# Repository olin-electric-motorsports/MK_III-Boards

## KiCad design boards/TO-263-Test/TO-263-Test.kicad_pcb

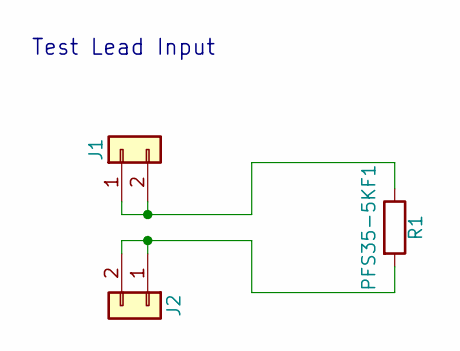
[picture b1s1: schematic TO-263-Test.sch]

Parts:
J1, J2: Conn_01x02; Pin_Header_Straight_1x02_Pitch2.54mm
R1: PFS35-5KF1; TO-263-2-Heatsink

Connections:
unnamed: J1.1, J1.2, R1.1
unnamed: J2.1, J2.2, R1.2

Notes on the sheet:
Test Lead Input

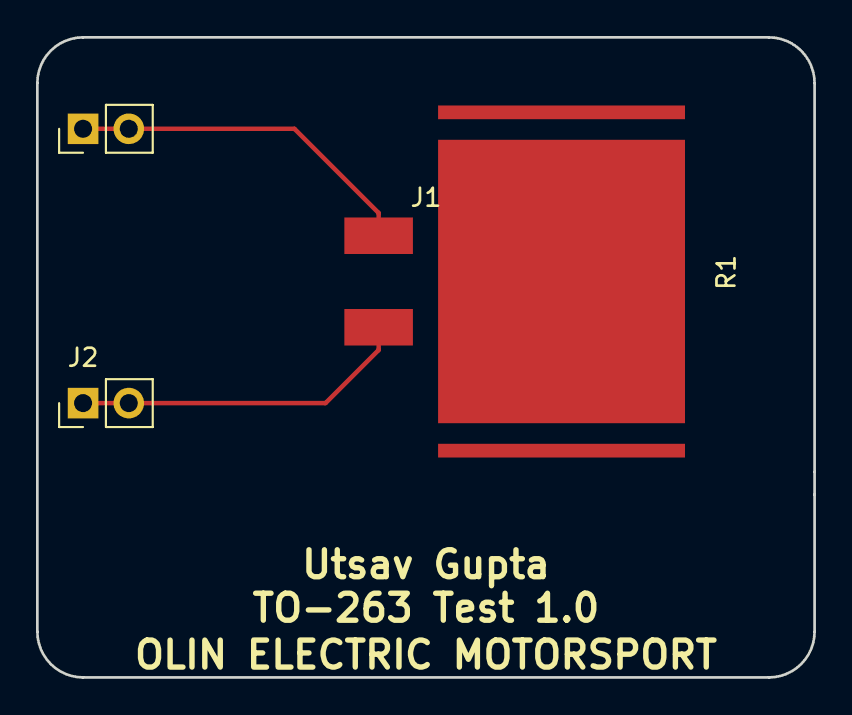
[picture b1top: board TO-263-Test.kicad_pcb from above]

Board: 2 copper layers, 43.2 x 35.6 mm, 3 parts (0 on the bottom side), 2 nets.

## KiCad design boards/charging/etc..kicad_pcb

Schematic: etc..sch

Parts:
C1, C2, C8, C9, C10: C_0.1uF; C_0805_OEM; MPN 478-3352-1-ND
C3: C_100pF; C_0805_OEM; MPN 399-1122-1-ND
C4, C5, C6, C7: C_30pF; C_0805_OEM; MPN 1276-1130-1-ND
C11: C_1uF; C_0805_OEM; MPN 478-10487-1-ND
C12: C_47uF; C_0805_OEM; MPN 587-4280-1-ND
C13: C_22uF; C_0805_OEM; MPN 1276-2725-1-ND
D1, D2, D3, D4, D8, D9: LED_0805; LED_0805_OEM; MPN 475-1410-1-ND
D7: D_Zener_18V; DO-214AA; MPN SMBJ5355B-TPMSCT-ND
F1: F_500mA_16V; Fuse_1210; MPN 507-1786-1-ND
IC1: ATMEGA16M1; TQFP-32_7x7mm_Pitch0.8mm; MPN ATMEGA16M1-AU-ND
J1: LCD screen; micromatch_female_vert_16; MPN A116164CT-ND
J2: Ampseal_8
J3, J4: Ultrafit_4; MPN WM11574-ND
L1: L_4.7uH; 4.7uH_Inductor_OEM; MPN 445-6583-1-ND
P1, P2: CONN_02X03; Pin_Header_Straight_2x03; MPN 609-3234-ND
R1: R_100; R_0805_OEM; MPN RNCP0805FTD100RCT-ND
R2, R3, R6, R16, R17: R_10k; R_0805_OEM; MPN CRS0805-FX-1002ELFCT-ND
R4, R5, R7, R8, R9, R10, R14: R_200; R_0805_OEM; MPN RMCF0805JT200RCT-ND
R13: R_0_Jumper; R_2512_OEM; MPN A121322CT-ND
R15: R_55.1k; R_0805_OEM; MPN 311-51.1KCRCT-ND
R18: R_1k; R_0805_OEM; MPN RNCP0805FTD1K00CT-ND
RV1: POT_TRIM-device; Potentiometer_Trimmer_Bourns_TCC3
U1: ATMEGA328P-AU; TQFP-32_7x7mm_Pitch0.8mm
U2: CAN_Transceiver; SOIC-8_3.9x4.9mm_Pitch1.27mm_OEM; MPN MCP2561-E/SN-ND
U3: RJ45_VT; RJ45-Vertical; MPN MRJ-5481-01-ND
U4: TPS561201; SOT-23-6_OEM; MPN TPS561201
Y1, Y2: Crystal_SMD; Crystal_SMD_FA238; MPN SER3686CT-ND

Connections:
+12V: D7.1, F1.1, J2.3, J2.5
AMS: IC1.15, J3.3
CANH: J2.4, J2.6, U2.7, U3.2
CANL: J2.7, J2.8, U2.6, U3.1
DATA: IC1.16, R3.1, U1.14
DB0: IC1.28, J1.7
DB1: IC1.27, J1.8
DB2: IC1.26, J1.9
DB3: IC1.25, J1.10
DB4: IC1.24, J1.11
DB5: IC1.23, J1.12
DB6: IC1.22, J1.13
DB7: IC1.18, J1.14
E: IC1.29, J1.6
GND: C1.2, C2.2, C3.2, C4.2, C5.2, C6.2, C7.2, C8.2, C9.1, C11.1, C12.2, C13.2, D1.1, D2.1, D3.1, D4.1, D7.2, D8.1, D9.1, IC1.5, IC1.20, J1.1, J1.16, J2.1, J2.2, J3.2, J3.4, J4.2, P1.6, P2.6, R17.2, RV1.3, U1.3, U1.5, U1.21, U2.2, U2.8, U3.8, U3.9, U3.11, U3.13, U3.14, U4.1, Y1.2, Y1.4, Y2.2, Y2.4
IMD: IC1.14, J3.1
LED1: R8.1, U3.10
LED2: R7.1, U3.12
LED5: R10.1, U1.23
LED6: R9.1, U1.24
MISO: IC1.1, P1.1, P2.1, U1.16, U3.5
MOSI: IC1.2, P1.4, P2.4, U1.15, U3.6
unnamed: C3.1, IC1.19, R1.2
unnamed: C4.1, IC1.11, Y1.1
unnamed: C6.1, IC1.10, Y1.3
unnamed: C10.1, U4.6
unnamed: C10.2, L1.1, U4.2
unnamed: C9.2, C11.2, C12.1, L1.2, R13.2, R15.2
unnamed: C13.1, F1.2, R16.1, R18.1, U4.3
unnamed: D1.2, R5.1
unnamed: D2.2, R4.1
unnamed: D3.2, R9.2
unnamed: D4.2, R10.2
unnamed: D8.2, R14.2
unnamed: D9.2, R18.2
unnamed: IC1.3, R5.2
unnamed: IC1.8, R8.2
unnamed: IC1.9, R7.2
unnamed: IC1.17, R4.2
unnamed: J1.3, RV1.2
unnamed: R15.1, R17.1, U4.4
unnamed: R16.2, U4.5
R/W: IC1.30, J1.5
RESET: IC1.31, P2.5, R6.2, U3.3
RS: IC1.32, J1.4
RST32: P1.5, R2.2, U1.29
RXCAN: IC1.7, U2.4
SCK: IC1.12, P1.3, P2.3, U1.17, U3.4
SCL: J4.4, U1.28
SDA: J4.3, U1.27
TXCAN: IC1.6, U2.1
VCC: C1.1, C2.1, C8.1, IC1.4, J1.2, J1.15, J4.1, P1.2, P2.2, R1.1, R2.1, R3.2, R6.1, R13.1, R14.1, RV1.1, U1.4, U1.6, U1.18, U1.20, U2.3, U3.7
XTAL1: C7.1, U1.7, Y2.3
XTAL2: C5.1, U1.8, Y2.1

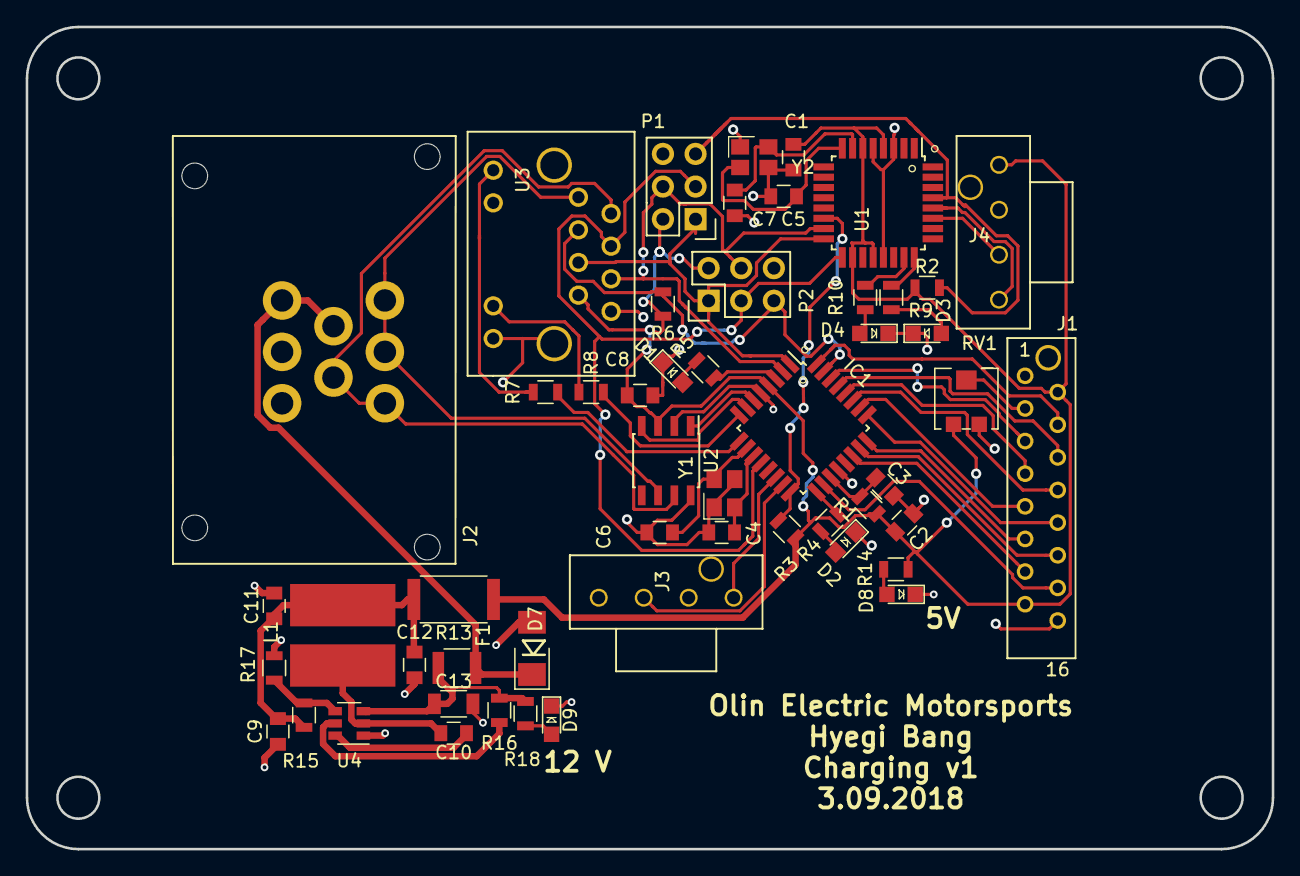
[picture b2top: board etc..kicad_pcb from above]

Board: 2 copper layers, 97.0 x 64.0 mm, 52 parts (0 on the bottom side), 54 nets.

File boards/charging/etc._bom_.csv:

Component,Description,Part,References,Value,Footprint,Quantity Per PCB,Datasheet,Package,MPN,MFN,PurchasingLink,PurchasingLink2,MPN2
1,,C_0.1uF-formula-etc.-rescue,C1 C2 C8 C9 C10,C_0.1uF,C_0805_OEM,5,http://datasheets.avx.com/X7RDielectric.pdf,Value,478-3352-1-ND,Digi-Key,https://www.digikey.com/products/en?keywords=478-3352-1-ND,,
2,,C_100pF-formula-etc.-rescue,C3,C_100pF,C_0805_OEM,1,https://content.kemet.com/datasheets/KEM_C1003_C0G_SMD.pdf,Value,399-1122-1-ND,Digi-Key,https://www.digikey.com/product-detail/en/kemet/C0805C101J5G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,,
3,CAP CER 1UF 25V X7R 0805,C_1uF-formula-etc.-rescue,C11,C_1uF,C_0805_OEM,1,http://datasheets.avx.com/X7RDielectric.pdf,Value,478-10487-1-ND,Digi-Key,https://www.digikey.com/product-detail/en/avx-corporation/08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,,
4,,C_22uF-formula-etc.-rescue,C13,C_22uF,C_0805_OEM,1,http://www.samsungsem.com/kr/support/product-search/mlcc/__i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,Value,1276-2725-1-ND,Digi-Key,https://www.digikey.com/products/en?keywords=1276-2725-1-ND,,
5,,C_30pF-formula-etc.-rescue,C4 C5 C6 C7,C_30pF,C_0805_OEM,4,https://media.digikey.com/pdf/Data%20Sheets/Samsung%20PDFs/C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,Value,1276-1130-1-ND,Digi-Key,https://www.digikey.com/product-detail/en/samsung-electro-me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,,
6,,C_47uF-formula-etc.-rescue,C12,C_47uF,C_0805_OEM,1,http://www.yuden.co.jp/productdata/catalog/en/mlcc_all_e.pdf,Value,587-4280-1-ND,Digi-Key,https://www.digikey.com/product-detail/en/taiyo-yuden/JMK212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,,
7,,D_Zener_18V-formula-etc.-rescue,D7,D_Zener_18V,DO-214AA,1,http://www.mccsemi.com/up_pdf/SMBJ5338B-SMBJ5388B(SMB).pdf,DO-214AA (SMB),SMBJ5355B-TPMSCT-ND,Digi-Key,https://www.digikey.com/products/en?keywords=SMBJ5355B-TPMSCT-ND,,
8,,LED_0805-formula-etc.-rescue,D1 D2 D3 D4 D8 D9,LED_0805,LED_0805_OEM,6,http://www.osram-os.com/Graphics/XPic9/00078860_0.pdf,Value,475-1410-1-ND,Digi-Key,https://www.digikey.com/products/en?keywords=475-1410-1-ND,,
9,,F_500mA_16V-formula-etc.-rescue,F1,F_500mA_16V,Fuse_1210,1,https://belfuse.com/resources/CircuitProtection/datasheets/0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,Value,507-1786-1-ND,Digi-Key,https://www.digikey.com/product-detail/en/bel-fuse-inc/0ZCH0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,,
10,,ATMEGA16M1-formula-etc.-rescue,IC1,ATMEGA16M1,TQFP-32_7x7mm_Pitch0.8mm,1,http://www.atmel.com/Images/Atmel-8209-8-bit%20AVR%20ATmega1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,Value,ATMEGA16M1-AU-ND,Digi-Key,https://www.digikey.com/product-detail/en/atmel/ATMEGA16M1-A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,,
11,Waterproof Panel-Mount Connector RA 8 Pin,Ampseal_8,J2,Ampseal_8,Ampseal_8,1,,,,,,,
12,,micromatch_male_16-formula-etc.-rescue,J1,LCD screen,micromatch_female_vert_16,1,,Value,A116164CT-ND,Digi-Key,https://www.digikey.com/product-detail/en/te-connectivity-am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,,
13,Ultrafit 4 Pin Connector,Ultrafit_4,J3 J4,Ultrafit_4,Ultrafit_4,2,http://www.literature.molex.com/SQLImages/kelmscott/Molex/PD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,Value,WM11574-ND,Digi-Key,https://www.digikey.com/products/en?keywords=WM11574-ND,https://www.digikey.com/product-detail/en/molex-llc/17225610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,WM11564-ND
14,,L_4.7uH-formula-etc.-rescue,L1,L_4.7uH,4.7uH_Inductor_OEM,1,https://product.tdk.com/info/en/documents/wdcatalog/withdraw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,Value,445-6583-1-ND,Digi-Key,https://www.digikey.com/product-detail/en/tdk-corporation/VL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,,
15,,CONN_02X03-formula-etc.-rescue,P1 P2,CONN_02X03,Pin_Header_Straight_2x03,2,http://portal.fciconnect.com/Comergent//fci/drawing/67996.pdf,Value,609-3234-ND,Digi-Key,https://www.digikey.com/product-detail/en/amphenol-fci/67997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,,
16,,R_0_Jumper-formula-etc.-rescue,R13,R_0_Jumper,R_2512_OEM,1,http://www.te.com/commerce/DocumentDelivery/DDEController?Ac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,Value,A121322CT-ND,Digi-Key,https://www.digikey.com/products/en?keywords=A121322CT-ND,,
17,,R_100-formula-etc.-rescue,R1,R_100,R_0805_OEM,1,https://www.seielect.com/Catalog/SEI-rncp.pdf,Value,RNCP0805FTD100RCT-ND,Digi-Key,https://www.digikey.com/products/en?keywords=RNCP0805FTD100RCT-ND,,
18,,R_10k-formula-etc.-rescue,R2 R3 R6 R16 R17,R_10k,R_0805_OEM,5,http://www.bourns.com/data/global/pdfs/CRS.pdf,Value,CRS0805-FX-1002ELFCT-ND,Digi-Key,https://www.digikey.com/products/en?keywords=CRS0805-FX-1002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,,
19,,R_1k-formula-etc.-rescue,R18,R_1k,R_0805_OEM,1,https://www.seielect.com/Catalog/SEI-rncp.pdf,Value,RNCP0805FTD1K00CT-ND,Digi-Key,https://www.digikey.com/products/en?keywords=RNCP0805FTD1K00CT-ND,,
20,,R_200-formula-etc.-rescue,R4 R5 R7 R8 R9 R10 R14,R_200,R_0805_OEM,7,https://www.seielect.com/Catalog/SEI-RMCF_RMCP.pdf,Value,RMCF0805JT200RCT-ND,Digi-Key,https://www.digikey.com/products/en?keywords=RMCF0805JT200RCT-ND,,
21,,R_55.1k-formula-etc.-rescue,R15,R_55.1k,R_0805_OEM,1,http://www.yageo.com.tw/exep/pages/download/literatures/PYu-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,Value,311-51.1KCRCT-ND,Digi-Key,https://www.digikey.com/products/en?keywords=311-51.1KCRCT-ND,,
22,,POT_TRIM-device-etc.-rescue,RV1,POT_TRIM-device,Potentiometer_Trimmer_Bourns_TCC3,1,,,,,,,
23,,ATMEGA328P-AU-atmel-etc.-rescue,U1,ATMEGA328P-AU,TQFP-32_7x7mm_Pitch0.8mm,1,http://www.atmel.com/images/atmel-8271-8-bit-avr-microcontro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,,,,,,
24,,CAN_Transceiver-formula-etc.-rescue,U2,CAN_Transceiver,SOIC-8_3.9x4.9mm_Pitch1.27mm_OEM,1,http://www.microchip.com/mymicrochip/filehandler.aspx?ddocna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,Value,MCP2561-E/SN-ND,Digi-Key,https://www.digikey.com/products/en?keywords=mcp2561-e%2Fsn,,
25,CONN MOD JACK 8P8C VERT UNSHLD,RJ45_VT,U3,RJ45_VT,RJ45-Vertical,1,https://www.amphenolcanada.com/ProductSearch/drawings/AC/MRJ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,,MRJ-5481-01-ND,Digi-Key,https://www.digikey.com/products/en?keywords=MRJ-5481-01,,
26,,TPS561201-formula-etc.-rescue,U4,TPS561201,SOT-23-6_OEM,1,http://www.ti.com/lit/ds/symlink/tps561201.pdf,Value,TPS561201,Digi-Key,https://www.digikey.com/products/en?keywords=296-46928-1-ND,,
27,,Crystal_SMD-formula-etc.-rescue,Y1 Y2,Crystal_SMD,Crystal_SMD_FA238,2,https://support.epson.biz/td/api/doc_check.php?dl=brief_FA-2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,Value,SER3686CT-ND,Digi-Key,https://www.digikey.com/products/en?keywords=SER3686CT-ND,,





Component Groups:,27
Component Count:,52
Fitted Components:,52
Number of PCBs:,1
Total components:,52
Schematic Version:,
Schematic Date:,
BoM Date:,Thu 08 Mar 2018 08:58:53 PM EST
Schematic Source:,/home/hyegibang/Formula/MK_III-Boards/boards/charging/etc..sch
KiCad Version:,Eeschema 5.0-dev-unknown-dd04bcb~61~ubuntu16.04.1

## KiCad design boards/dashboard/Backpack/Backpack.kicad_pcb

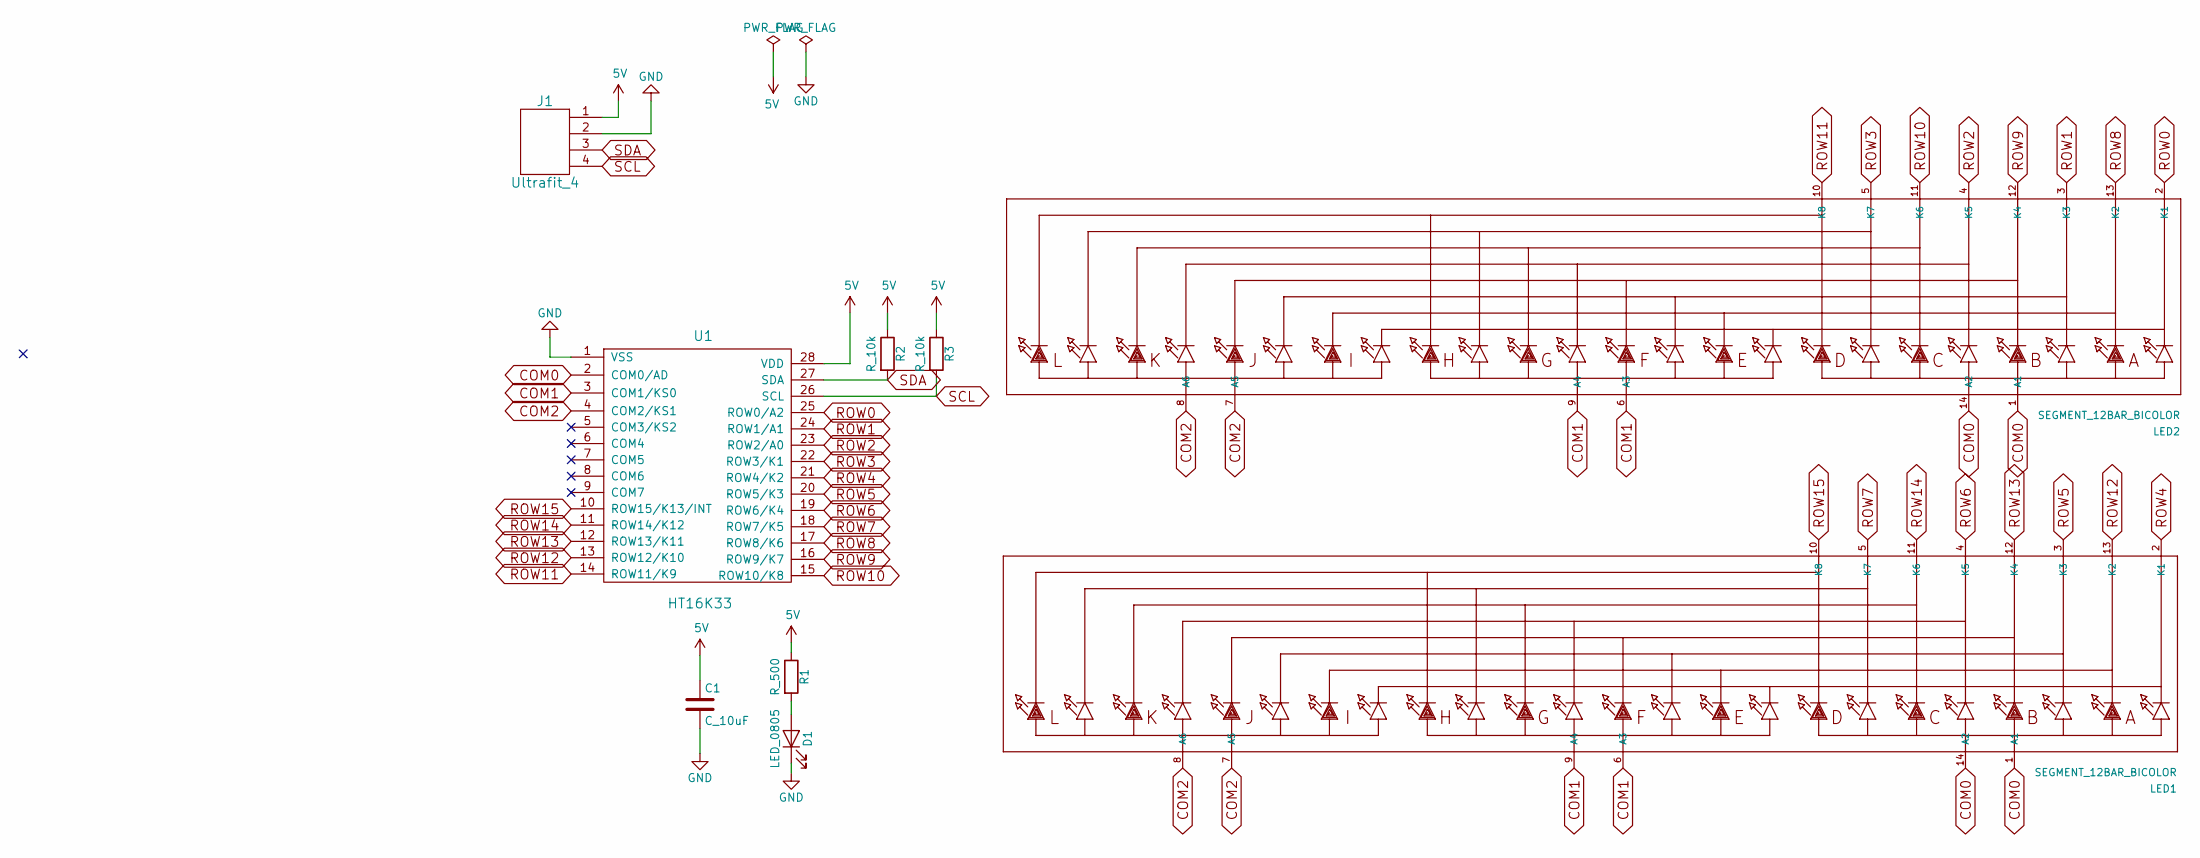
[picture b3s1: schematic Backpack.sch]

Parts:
C1: C_10uF; C_0805_OEM; MPN 478-5167-1-ND
D1: LED_0805; LED_0805_OEM; MPN 475-1410-1-ND
J1: Ultrafit_4; MPN WM11574-ND
LED1, LED2: SEGMENT_12BAR_BICOLOR; SEGMENT_BICOL_BL-AR12Z3010
R1: R_500; R_0805_OEM; MPN 541-1905-2-ND
R2, R3: R_10k; R_0805_OEM; MPN CRS0805-FX-1002ELFCT-ND
U1: HT16K33; SOP28

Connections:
5V: C1.1, J1.1, R1.1, R2.1, R3.1, U1.28 (VDD)
COM0: LED1.1 (A1), LED1.14 (A2), LED2.1 (A1), LED2.14 (A2), U1.2 (COM0/AD)
COM1: LED1.6 (A3), LED1.9 (A4), LED2.6 (A3), LED2.9 (A4), U1.3 (COM1/KS0)
COM2: LED1.7 (A5), LED1.8 (A6), LED2.7 (A5), LED2.8 (A6), U1.4 (COM2/KS1)
GND: C1.2, D1.1 (K), J1.2, U1.1 (VSS)
unnamed: D1.2 (A), R1.2
ROW0: LED2.2 (K1), U1.25 (ROW0/A2)
ROW1: LED2.3 (K3), U1.24 (ROW1/A1)
ROW2: LED2.4 (K5), U1.23 (ROW2/A0)
ROW3: LED2.5 (K7), U1.22 (ROW3/K1)
ROW4: LED1.2 (K1), U1.21 (ROW4/K2)
ROW5: LED1.3 (K3), U1.20 (ROW5/K3)
ROW6: LED1.4 (K5), U1.19 (ROW6/K4)
ROW7: LED1.5 (K7), U1.18 (ROW7/K5)
ROW8: LED2.13 (K2), U1.17 (ROW8/K6)
ROW9: LED2.12 (K4), U1.16 (ROW9/K7)
ROW10: LED2.11 (K6), U1.15 (ROW10/K8)
ROW11: LED2.10 (K8), U1.14 (ROW11/K9)
ROW12: LED1.13 (K2), U1.13 (ROW12/K10)
ROW13: LED1.12 (K4), U1.12 (ROW13/K11)
ROW14: LED1.11 (K6), U1.11 (ROW14/K12)
ROW15: LED1.10 (K8), U1.10 (ROW15/K13/INT)
SCL: J1.4, R3.2, U1.26 (SCL)
SDA: J1.3, R2.2, U1.27 (SDA)

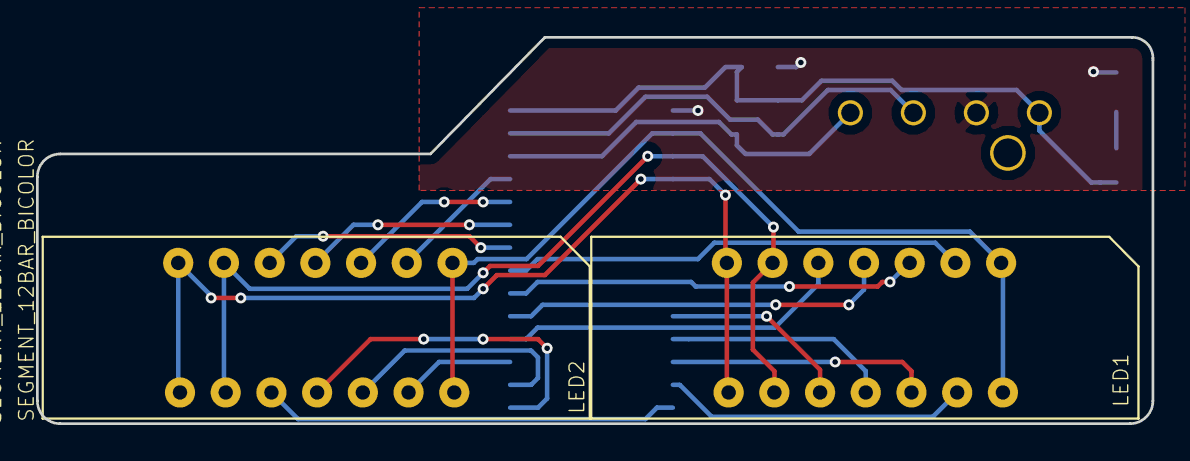
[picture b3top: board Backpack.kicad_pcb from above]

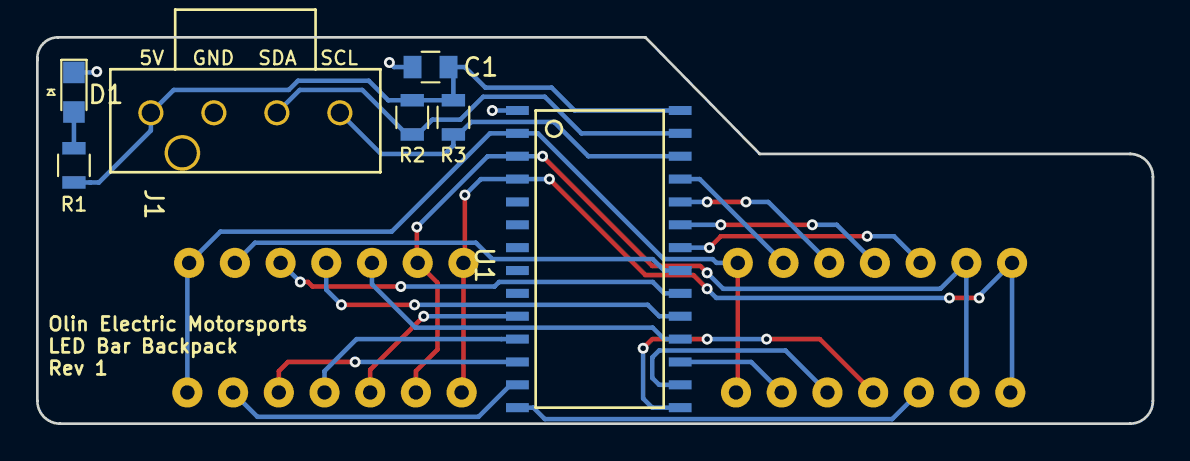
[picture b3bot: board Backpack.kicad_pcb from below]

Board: 2 copper layers, 62.0 x 21.5 mm, 9 parts (7 on the bottom side), 24 nets.

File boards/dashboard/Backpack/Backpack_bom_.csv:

Component,Description,Part,References,Value,Footprint,Quantity Per PCB,Datasheet,Package,MPN,MFN,PurchasingLink,PurchasingLink2,MPN2
1,CAP CER 10UF 10V X5R 0805,C_10uF,C1,C_10uF,C_0805_OEM,1,http://datasheets.avx.com/cx5r.pdf,Value,478-5167-1-ND,Digi-Key,https://www.digikey.com/product-detail/en/avx-corporation/08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,,
2,LED_0805,LED_0805,D1,LED_0805,LED_0805_OEM,1,http://www.osram-os.com/Graphics/XPic9/00078860_0.pdf,Value,475-1410-1-ND,Digi-Key,https://www.digikey.com/products/en?keywords=475-1410-1-ND,,
3,Ultrafit 4 Pin Connector,Ultrafit_4,J1,Ultrafit_4,Ultrafit_4,1,http://www.literature.molex.com/SQLImages/kelmscott/Molex/PD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,Value,WM11574-ND,Digi-Key,https://www.digikey.com/products/en?keywords=WM11574-ND,https://www.digikey.com/product-detail/en/molex-llc/17225610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,WM11564-ND
4,,SEGMENT_12BAR_BICOLOR,LED1 LED2,SEGMENT_12BAR_BICOLOR,SEGMENT_BICOL_BL-AR12Z3010,2,,,,,,,
5,Res 10k 1%,R_10k,R2 R3,R_10k,R_0805_OEM,2,http://www.bourns.com/data/global/pdfs/CRS.pdf,Value,CRS0805-FX-1002ELFCT-ND,Digi-Key,https://www.digikey.com/products/en?keywords=CRS0805-FX-1002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,,
6,Resistor 500Ohm 0.1% Tolerance,R_500,R1,R_500,R_0805_OEM,1,http://www.vishay.com/docs/60057/pnm.pdf,Value,541-1905-2-ND,Digi Key,https://www.digikey.com/product-detail/en/vishay-dale/PNM040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,,
7,,HT16K33,U1,HT16K33,SOP28,1,,,,,,,





Component Groups:,7
Component Count:,9
Fitted Components:,9
Number of PCBs:,1
Total components:,9
Schematic Version:,
Schematic Date:,
BoM Date:,Wed 21 Feb 2018 10:12:43 PM EST
Schematic Source:,/home/lanfenson/MK_III-Boards-master/boards/dashboard/Backpack/Backpack.sch
KiCad Version:,Eeschema 4.0.7-e2-6376~58~ubuntu16.04.1

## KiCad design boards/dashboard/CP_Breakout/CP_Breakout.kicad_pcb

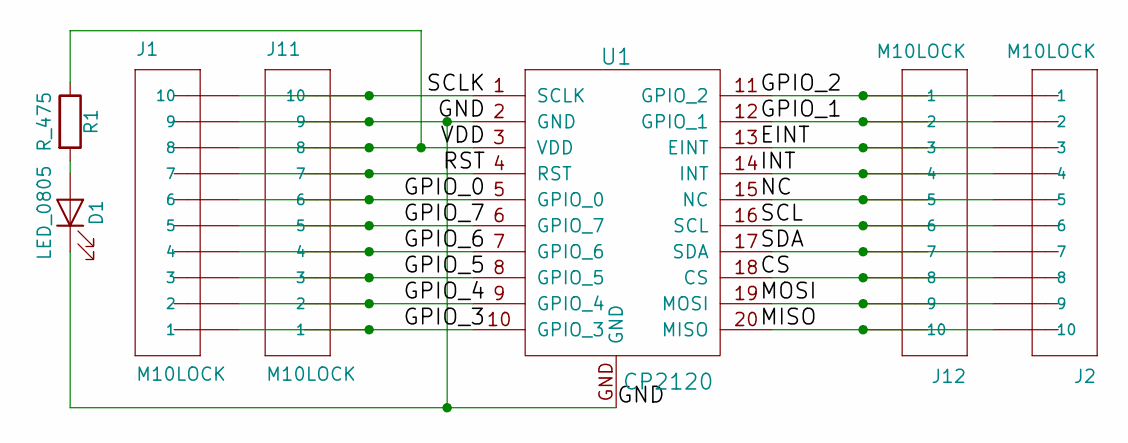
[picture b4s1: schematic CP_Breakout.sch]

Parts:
D1: LED_0805; LED_0805_OEM; MPN 475-1410-1-ND
J1, J2, J11, J12: M10LOCK; 1X10_LOCK
R1: R_475; R_0805_OEM; MPN 311-475CRCT-ND
U1: CP2120; CP2120-QFN; MPN 336-1324-ND

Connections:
/GND: D1.1 (K), J1.9, J11.9, U1.2 (GND), U1.GND
unnamed: D1.2 (A), R1.2
unnamed: J1.1, J11.1, U1.10 (GPIO_3)
unnamed: J1.2, J11.2, U1.9 (GPIO_4)
unnamed: J1.3, J11.3, U1.8 (GPIO_5)
unnamed: J1.4, J11.4, U1.7 (GPIO_6)
unnamed: J1.5, J11.5, U1.6 (GPIO_7)
unnamed: J1.6, J11.6, U1.5 (GPIO_0)
unnamed: J1.7, J11.7, U1.4 (RST)
unnamed: J1.8, J11.8, R1.1, U1.3 (VDD)
unnamed: J1.10, J11.10, U1.1 (SCLK)
unnamed: J2.1, J12.1, U1.11 (GPIO_2)
unnamed: J2.2, J12.2, U1.12 (GPIO_1)
unnamed: J2.3, J12.3, U1.13 (EINT)
unnamed: J2.4, J12.4, U1.14 (INT)
unnamed: J2.5, J12.5, U1.15 (NC)
unnamed: J2.6, J12.6, U1.16 (SCL)
unnamed: J2.7, J12.7, U1.17 (SDA)
unnamed: J2.8, J12.8, U1.18 (CS)
unnamed: J2.9, J12.9, U1.19 (MOSI)
unnamed: J2.10, J12.10, U1.20 (MISO)

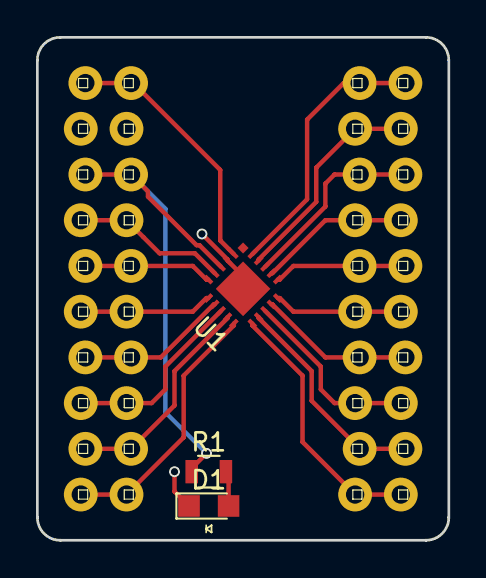
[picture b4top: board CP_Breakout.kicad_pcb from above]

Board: 2 copper layers, 22.9 x 27.9 mm, 7 parts (0 on the bottom side), 21 nets.

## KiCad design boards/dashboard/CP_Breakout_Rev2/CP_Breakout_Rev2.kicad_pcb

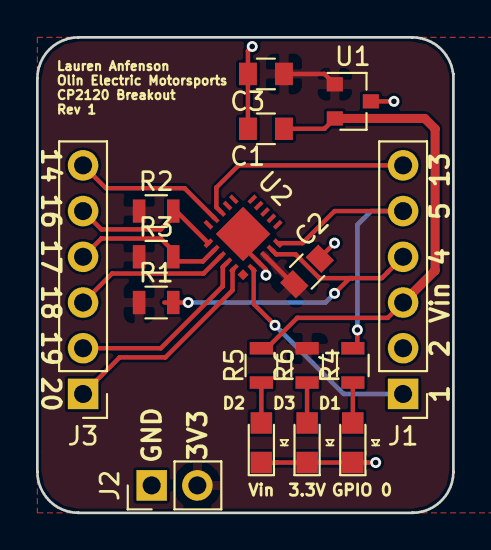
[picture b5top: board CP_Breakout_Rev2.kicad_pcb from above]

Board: 2 copper layers, 23.1 x 26.4 mm, 17 parts (0 on the bottom side), 16 nets.

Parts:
C1, C2, C3: C_0.1uF; C_0805_OEM
D1, D2, D3: LED_0805; LED_0805_OEM
J1, J3: Conn_01x06; Pin_Header_Straight_1x06_Pitch2.54mm
J2: Conn_01x02; Pin_Header_Straight_1x02_Pitch2.54mm
R1, R2, R3: 4.7kR; R_0805_OEM
R4, R5, R6: R_499; R_0805_OEM
U1: LM3480; SOT-23
U2: CP2120; CP2120-QFN

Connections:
+3V3: C2.1, C3.1, J2.2, R1.1, R2.1, R3.1, R6.1, U1.1, U2.3
CS: J3.3, U2.18
EINT: J1.6, U2.13
GND: C1.2, C2.2, C3.2, D1.1, D2.1, D3.1, J1.2, J2.1, U1.3, U2.2, U2.GND
GPIO_0: J1.5, R4.1, U2.5
INT: J3.6, U2.14
MISO: J3.1, U2.20
MOSI: J3.2, U2.19
unnamed: D1.2, R4.2
unnamed: D2.2, R5.2
unnamed: D3.2, R6.2
RST: J1.4, R1.2, U2.4
SCL: J3.5, R2.2, U2.16
SCLK: J1.1, U2.1
SDA: J3.4, R3.2, U2.17
VCC: C1.1, J1.3, R5.1, U1.2

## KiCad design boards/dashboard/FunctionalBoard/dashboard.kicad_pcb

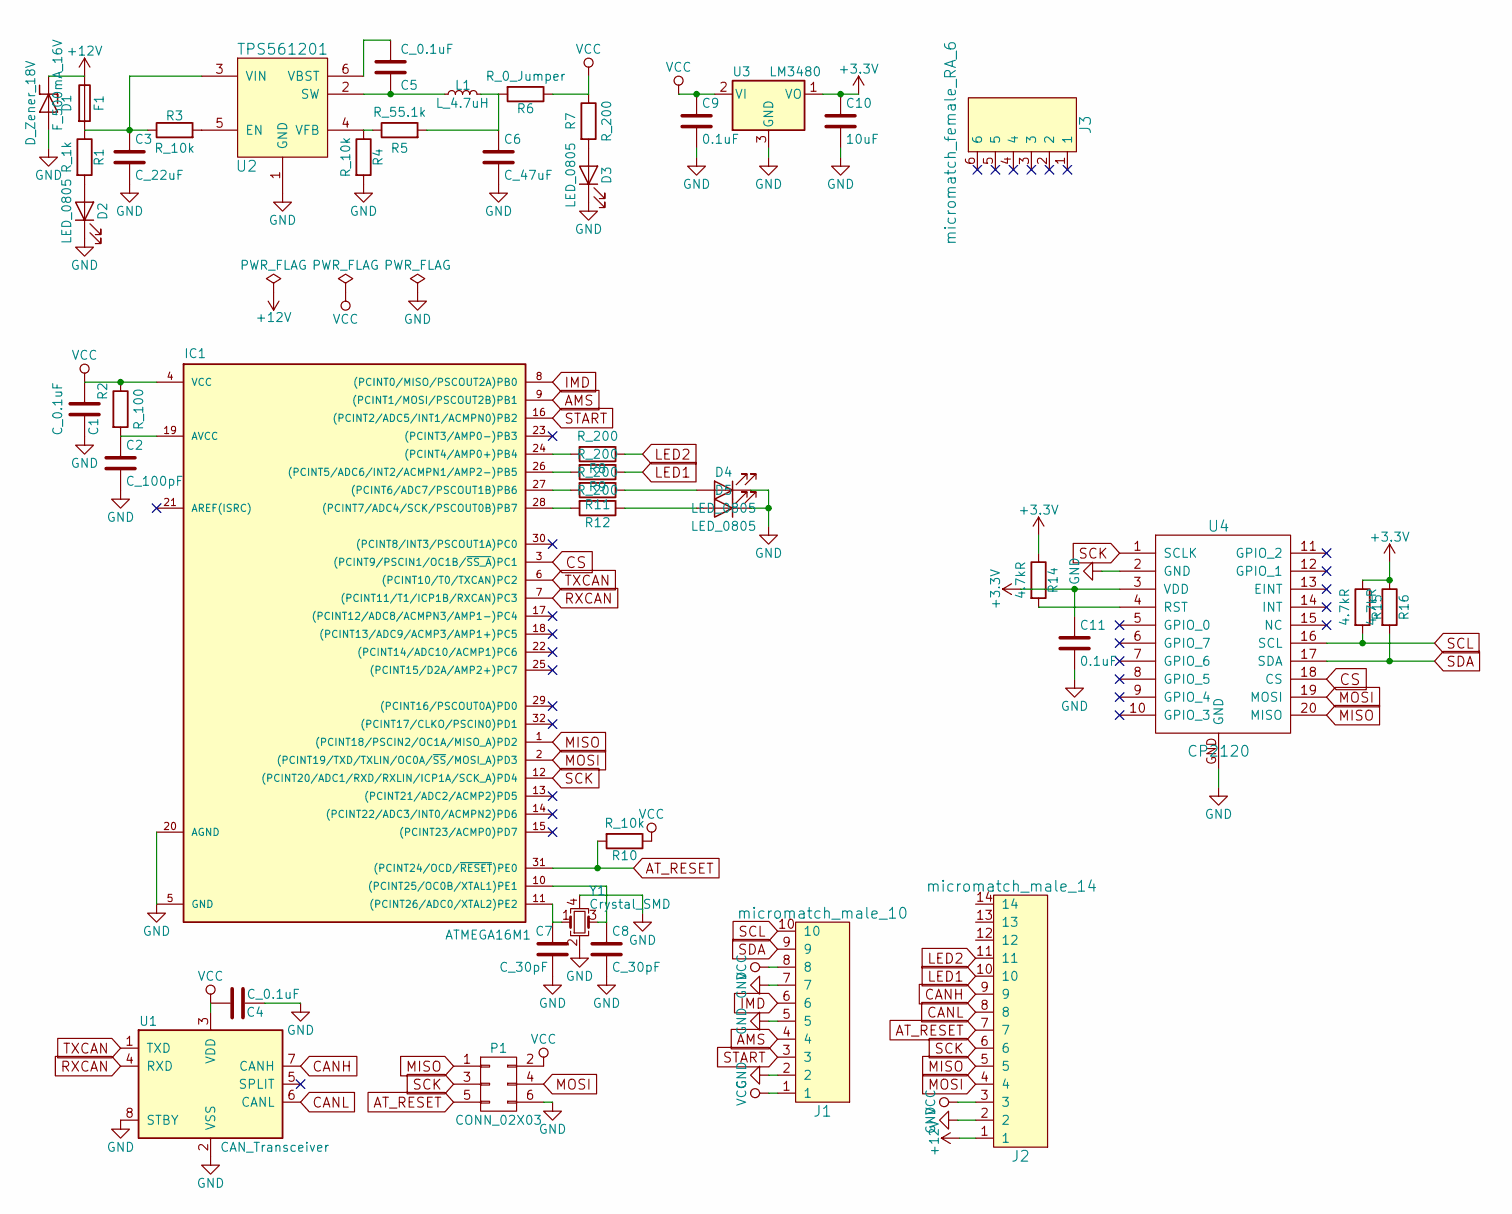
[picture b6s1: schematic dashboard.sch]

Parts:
C1, C4, C5: C_0.1uF; C_0805; MPN 478-3352-1-ND
C2: C_100pF; C_0805; MPN 399-1122-1-ND
C3: C_22uF; C_1206; MPN 1276-2725-1-ND
C6: C_47uF; C_0805; MPN 587-4280-1-ND
C7, C8: C_30pF; C_0805; MPN 1276-1130-1-ND
C9, C11: 0.1uF; C_0805; MPN 587-4280-1-ND
C10: 10uF; C_0805; MPN 587-4280-1-ND
D1: D_Zener_18V; DO-214AA; MPN SMBJ5355B-TPMSCT-ND
D2, D3, D4, D5: LED_0805; MPN 475-1410-1-ND
F1: F_500mA_16V; Fuse_1210; MPN 507-1786-1-ND
IC1: ATMEGA16M1; TQFP-32_7x7mm_Pitch0.8mm; MPN ATMEGA16M1-AU-ND
J1: micromatch_male_10; micromatch_female_ra_10; MPN A110881CT-ND
J2: micromatch_male_14; micromatch_female_ra_14; MPN A99442CT-ND
J3: micromatch_female_RA_6; micromatch_female_ra_6; MPN A99483CT-ND
L1: L_4.7uH; 4.7uH_Inductor_OEM; MPN 445-6583-1-ND
P1: CONN_02X03; Pin_Header_Straight_2x03; MPN 609-3234-ND
R1: R_1k; R_0805_OEM; MPN RNCP0805FTD1K00CT-ND
R2: R_100; R_0805; MPN RNCP0805FTD100RCT-ND
R3, R4, R10: R_10k; R_0805; MPN CRS0805-FX-1002ELFCT-ND
R5: R_55.1k; R_0805; MPN 311-51.1KCRCT-ND
R6: R_0_Jumper; R_2512; MPN A121322CT-ND
R7: R_200; R_0805; MPN RMCF0805JT200RCT-ND
R8, R9, R11, R12: R_200; R_0805_OEM; MPN RMCF0805JT200RCT-ND
R14, R15, R16: 4.7kR; R_0805_OEM
U1: CAN_Transceiver; SOIC-8_3.9x4.9mm_Pitch1.27mm; MPN MCP2561-E/SN-ND
U2: TPS561201; SOT-23-6; MPN TPS561201
U3: LM3480; SOT-23
U4: CP2120; CP2120-QFN
Y1: Crystal_SMD; Crystal_SMD_FA238; MPN SER3686CT-ND

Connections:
+3V3: C10.1, C11.1, R14.1, R15.1, R16.1, U3.1 (VO), U4.3 (VDD)
+12V: D1.1 (K), F1.1, J2.1
AMS: IC1.9 ((PCINT1/MOSI/PSCOUT2B)PB1), J1.4
AT_RESET: IC1.31 ((PCINT24/OCD/~RESET~)PE0), J2.7, P1.5, R10.2
CANH: J2.9, U1.7 (CANH)
CANL: J2.8, U1.6 (CANL)
CS: IC1.3 ((PCINT9/PSCIN1/OC1B/~SS_A~)PC1), U4.18 (CS)
GND: C1.2, C2.2, C3.2, C4.2, C6.2, C7.2, C8.2, C9.2, C10.2, C11.2, D1.2 (A), D2.1 (K), D3.1 (K), D4.1 (K), D5.1 (K), IC1.5 (GND), IC1.20 (AGND), J1.2, J1.5, J1.7, J2.2, P1.6, R4.2, U1.2 (VSS), U1.8 (STBY), U2.1 (GND), U3.3 (GND), U4.2 (GND), U4.GND, Y1.2, Y1.4
IMD: IC1.8 ((PCINT0/MISO/PSCOUT2A)PB0), J1.6
LED1: J2.10, R9.1
LED2: J2.11, R8.1
MISO: IC1.1 ((PCINT18/PSCIN2/OC1A/MISO_A)PD2), J2.5, P1.1, U4.20 (MISO)
MOSI: IC1.2 ((PCINT19/TXD/TXLIN/OC0A/~SS~/MOSI_A)PD3), J2.4, P1.4, U4.19 (MOSI)
unnamed: C2.1, IC1.19 (AVCC), R2.2
unnamed: C3.1, F1.2, R1.1, R3.1, U2.3 (VIN)
unnamed: C5.1, U2.6 (VBST)
unnamed: C5.2, L1.1, U2.2 (SW)
unnamed: C6.1, L1.2, R5.2, R6.2
unnamed: C7.1, IC1.11 ((PCINT26/ADC0/XTAL2)PE2), Y1.1
unnamed: C8.1, IC1.10 ((PCINT25/OC0B/XTAL1)PE1), Y1.3
unnamed: D2.2 (A), R1.2
unnamed: D3.2 (A), R7.2
unnamed: D4.2 (A), R11.1
unnamed: D5.2 (A), R12.1
unnamed: IC1.24 ((PCINT4/AMP0+)PB4), R8.2
unnamed: IC1.26 ((PCINT5/ADC6/INT2/ACMPN1/AMP2-)PB5), R9.2
unnamed: IC1.27 ((PCINT6/ADC7/PSCOUT1B)PB6), R11.2
unnamed: IC1.28 ((PCINT7/ADC4/SCK/PSCOUT0B)PB7), R12.2
unnamed: R3.2, U2.5 (EN)
unnamed: R4.1, R5.1, U2.4 (VFB)
unnamed: R14.2, U4.4 (RST)
RXCAN: IC1.7 ((PCINT11/T1/ICP1B/RXCAN)PC3), U1.4 (RXD)
SCK: IC1.12 ((PCINT20/ADC1/RXD/RXLIN/ICP1A/SCK_A)PD4), J2.6, P1.3, U4.1 (SCLK)
SCL: J1.10, R15.2, U4.16 (SCL)
SDA: J1.9, R16.2, U4.17 (SDA)
START: IC1.16 ((PCINT2/ADC5/INT1/ACMPN0)PB2), J1.3
TXCAN: IC1.6 ((PCINT10/T0/TXCAN)PC2), U1.1 (TXD)
VCC: C1.1, C4.1, C9.1, IC1.4 (VCC), J1.1, J1.8, J2.3, P1.2, R2.1, R6.1, R7.1, R10.1, U1.3 (VDD), U3.2 (VI)

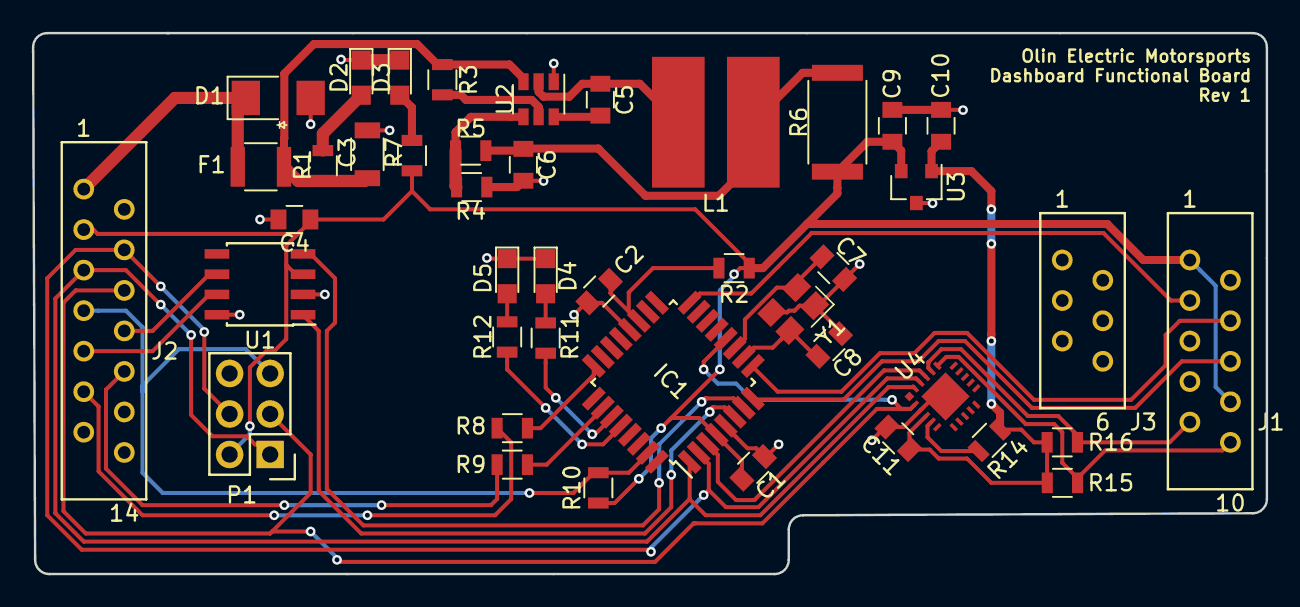
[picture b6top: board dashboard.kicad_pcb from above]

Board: 2 copper layers, 77.3 x 33.9 mm, 43 parts (0 on the bottom side), 38 nets.
